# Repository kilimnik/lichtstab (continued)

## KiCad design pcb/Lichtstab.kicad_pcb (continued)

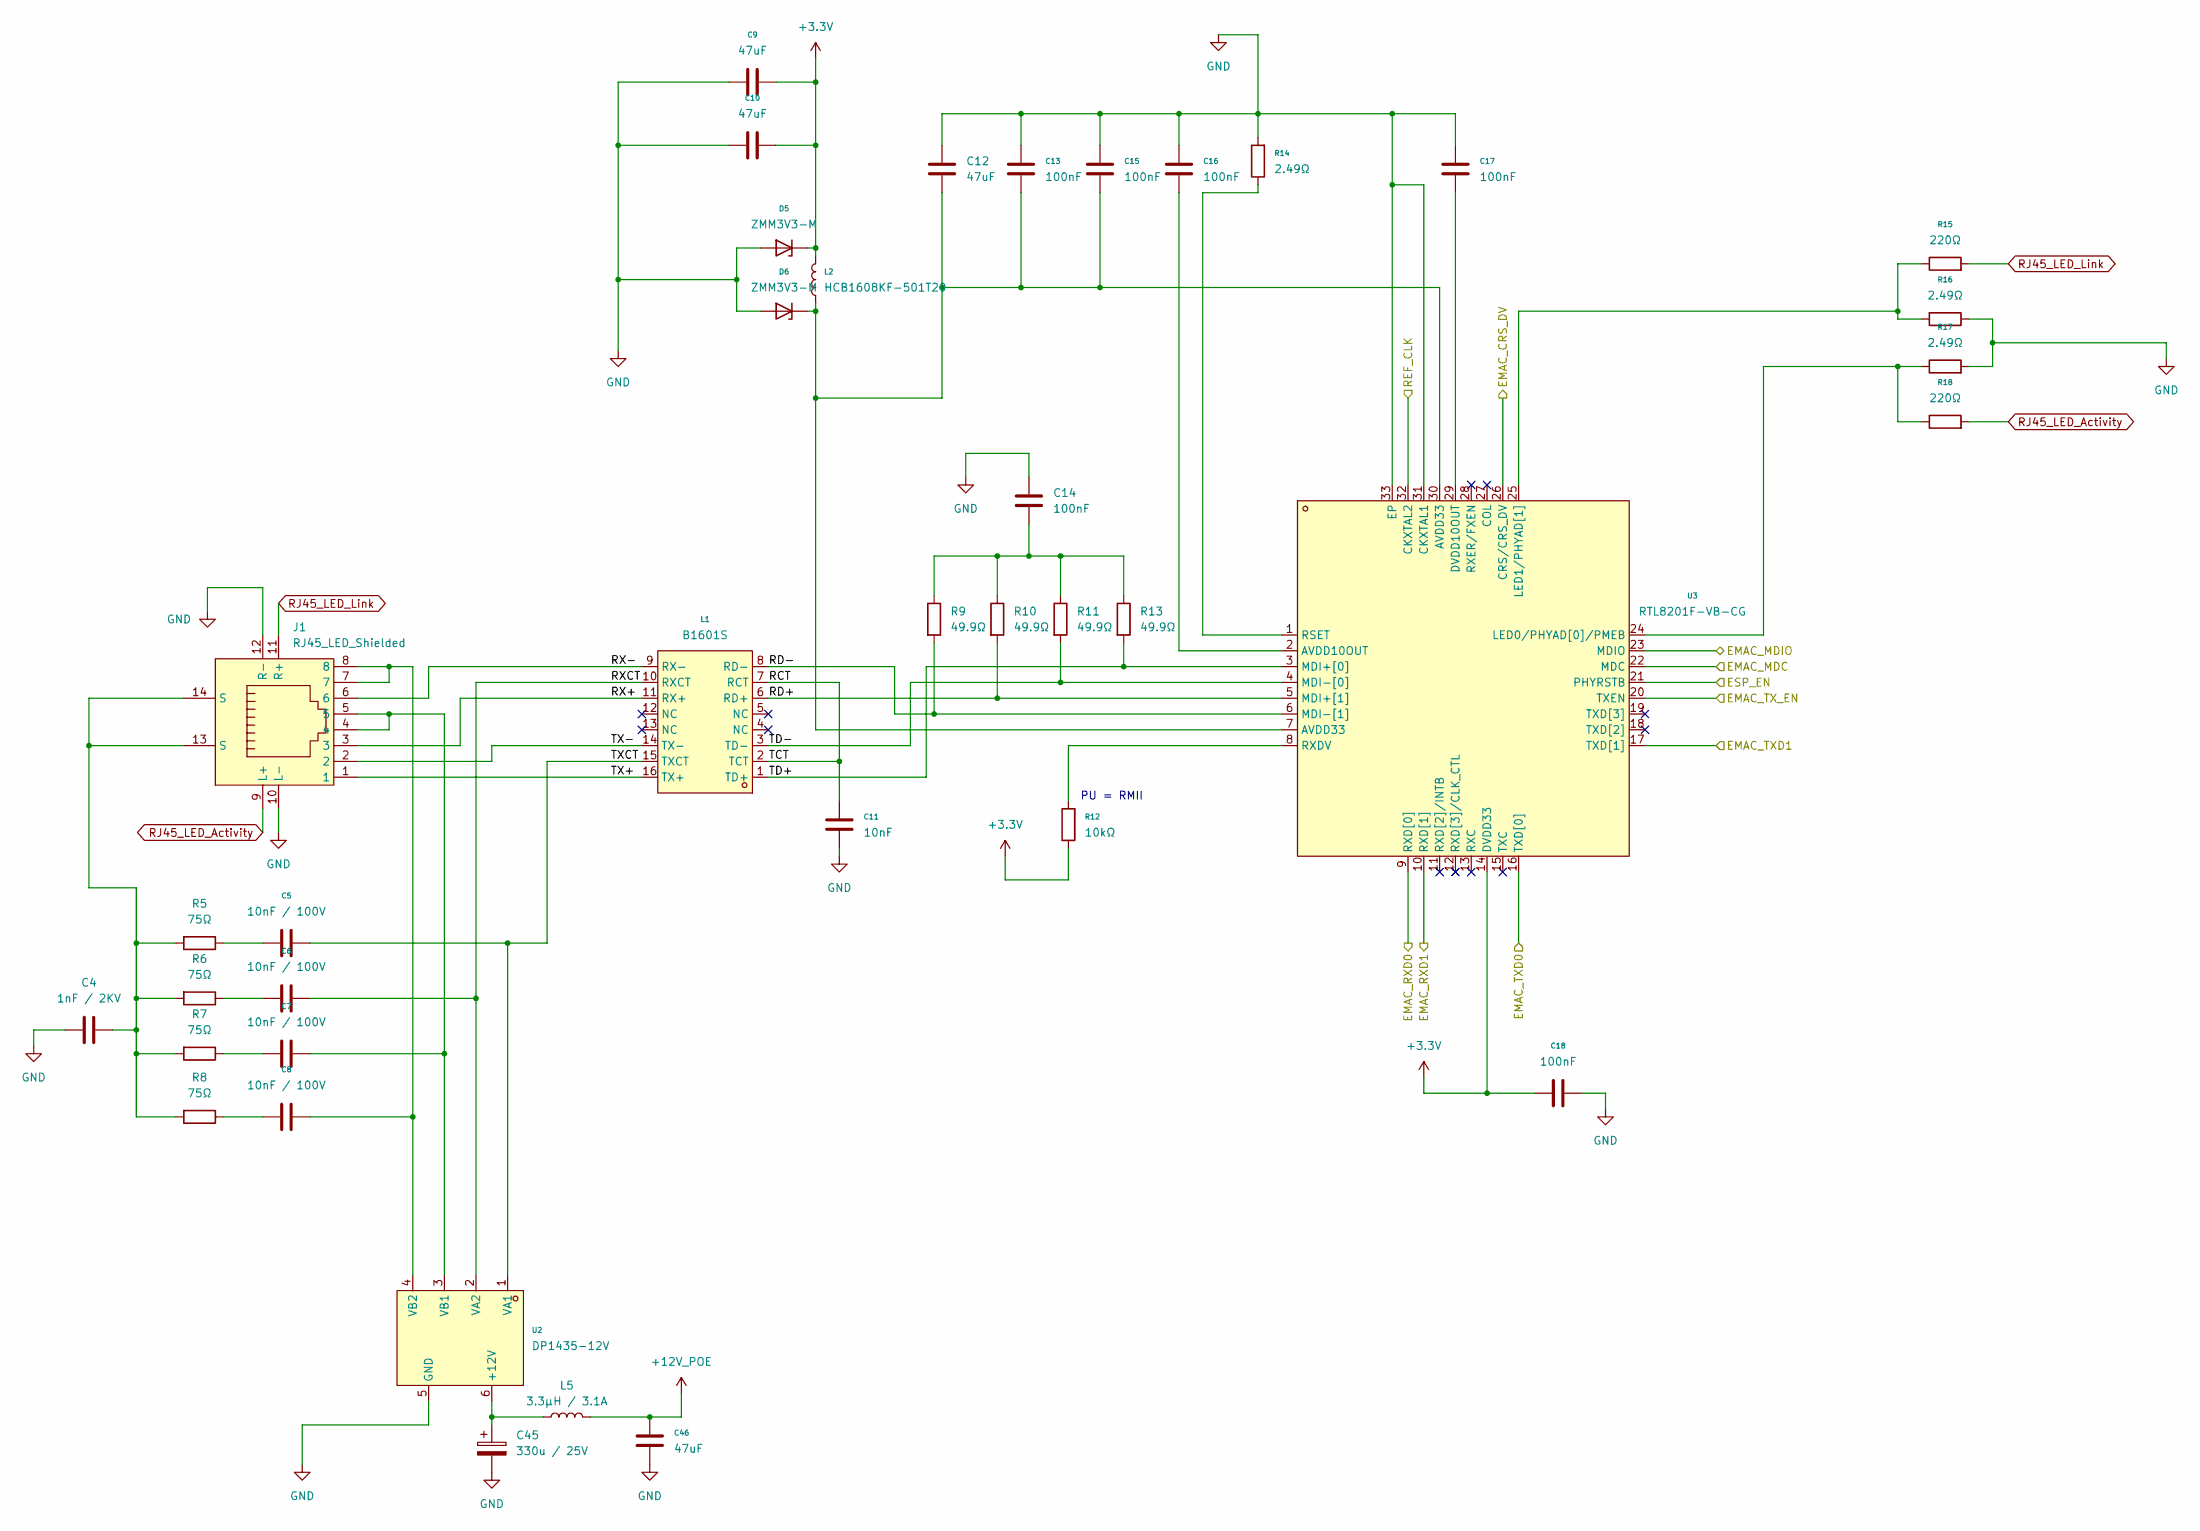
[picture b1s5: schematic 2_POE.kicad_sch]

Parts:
C4: 1nF / 2KV; C_1206_3216Metric
C5, C6, C7, C8: 10nF / 100V; C_0603_1608Metric; LCSC C43253
C9, C10, C12, C46: 47uF; C_1206_3216Metric; LCSC C22367835
C11: 10nF; C_0603_1608Metric; LCSC C43253
C13, C15, C16, C17, C18: 100nF; C_0603_1608Metric; LCSC C14663
C14: 100nF; C_0603_1608Metric
C45: 330u / 25V; CP_Elec_8x10.5; LCSC C335985
D5, D6: ZMM3V3-M; D_MiniMELF; LCSC C2891740
J1: RJ45_LED_Shielded; RJ45-TH_R-RJ45R08P-C000; LCSC Part C386757
L1: B1601S; SMD-16_L12.7-W7.0-P1.27-LS9.5-BL; LCSC C510548
L2: HCB1608KF-501T20; L_0603_1608Metric; LCSC C356977
L5: 3.3µH / 3.1A; L_Changjiang_FNR5030S; LCSC C2847470
R5, R6, R7, R8: 75Ω; R_0603_1608Metric; LCSC C4275
R9, R10, R11, R13: 49.9Ω; R_0402_1005Metric
R12: 10kΩ; R_0603_1608Metric; LCSC C25804
R14, R16, R17: 2.49Ω; R_0603_1608Metric; LCSC C22908
R15, R18: 220Ω; R_0603_1608Metric; LCSC C22962
U2: DP1435-12V; PWRM-TH_DP1435-XX; LCSC Part C5380098
U3: RTL8201F-VB-CG; TQFN-32-1EP_5x5mm_P0.5mm_EP3.4x3.4mm_ThermalVias; LCSC C45044

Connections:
+3.3V: C9.1, C10.1, C18.1, D5.1 (K), L2.2, R12.1, U3.14 (DVDD33); also elsewhere on the board
+12V_POE: C46.2, L5.2; also elsewhere on the board
/General/EMAC_CRS_DV: U3.26 (CRS/CRS_DV); also elsewhere on the board
/General/EMAC_MDC: U3.22 (MDC); also elsewhere on the board
/General/EMAC_MDIO: U3.23 (MDIO); also elsewhere on the board
/General/EMAC_RXD0: U3.9 (RXD[0]); also elsewhere on the board
/General/EMAC_RXD1: U3.10 (RXD[1]); also elsewhere on the board
/General/EMAC_TXD0: U3.16 (TXD[0]); also elsewhere on the board
/General/EMAC_TXD1: U3.17 (TXD[1]); also elsewhere on the board
/General/EMAC_TX_EN: U3.20 (TXEN); also elsewhere on the board
/General/ESP_EN: U3.21 (PHYRSTB); also elsewhere on the board
/General/REF_CLK: U3.32 (CKXTAL2); also elsewhere on the board
/POE/RCT: C11.2, L1.2 (TCT), L1.7 (RCT)
/POE/RD+: L1.6 (RD+), R10.2, U3.5 (MDI+[1])
/POE/RD-: L1.8 (RD-), R9.2, U3.6 (MDI-[1])
/POE/RX+: J1.3, L1.11 (RX+)
/POE/RX-: J1.6, L1.9 (RX-)
/POE/RXCT: C6.2, L1.10 (RXCT), U2.2 (VA2)
/POE/TD+: L1.1 (TD+), R13.2, U3.3 (MDI+[0])
/POE/TD-: L1.3 (TD-), R11.2, U3.4 (MDI-[0])
/POE/TX+: J1.1, L1.16 (TX+)
/POE/TX-: J1.2, L1.14 (TX-)
/POE/TXCT: C5.2, L1.15 (TXCT), U2.1 (VA1)
GND: C4.1, C9.2, C10.2, C11.1, C12.1, C13.1, C14.1, C15.1, C16.1, C17.1, C18.2, C45.2, C46.1, D5.2 (A), D6.2 (A), J1.10 (L-), J1.12 (R-), R14.2, R16.1, R17.2, U2.5 (GND), U3.31 (CKXTAL1), U3.33 (EP); also elsewhere on the board
unnamed: C4.2, J1.13 (S), J1.14 (S), R5.2, R6.2, R7.2, R8.2
unnamed: C5.1, R5.1
unnamed: C6.1, R6.1
unnamed: C7.1, R7.1
unnamed: C8.2, R8.1
unnamed: C14.2, R9.1, R10.1, R11.1, R13.1
unnamed: C12.2, C13.2, C15.2, D6.1 (K), L2.1, U3.7 (AVDD33), U3.30 (AVDD33)
unnamed: C45.1, L5.1, U2.6 (+12V)
unnamed: C7.2, J1.4, J1.5, U2.3 (VB1)
unnamed: C8.1, J1.7, J1.8, U2.4 (VB2)
unnamed: C16.2, U3.2 (AVDD10OUT)
unnamed: C17.2, U3.29 (DVDD10OUT)
unnamed: R17.1, R18.1, U3.24 (LED0/PHYAD[0]/PMEB)
unnamed: R15.1, R16.2, U3.25 (LED1/PHYAD[1])
unnamed: R14.1, U3.1 (RSET)
unnamed: R12.2, U3.8 (RXDV)
RJ45_LED_Activity: J1.9 (L+), R18.2
RJ45_LED_Link: J1.11 (R+), R15.2

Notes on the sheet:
PU = RMII

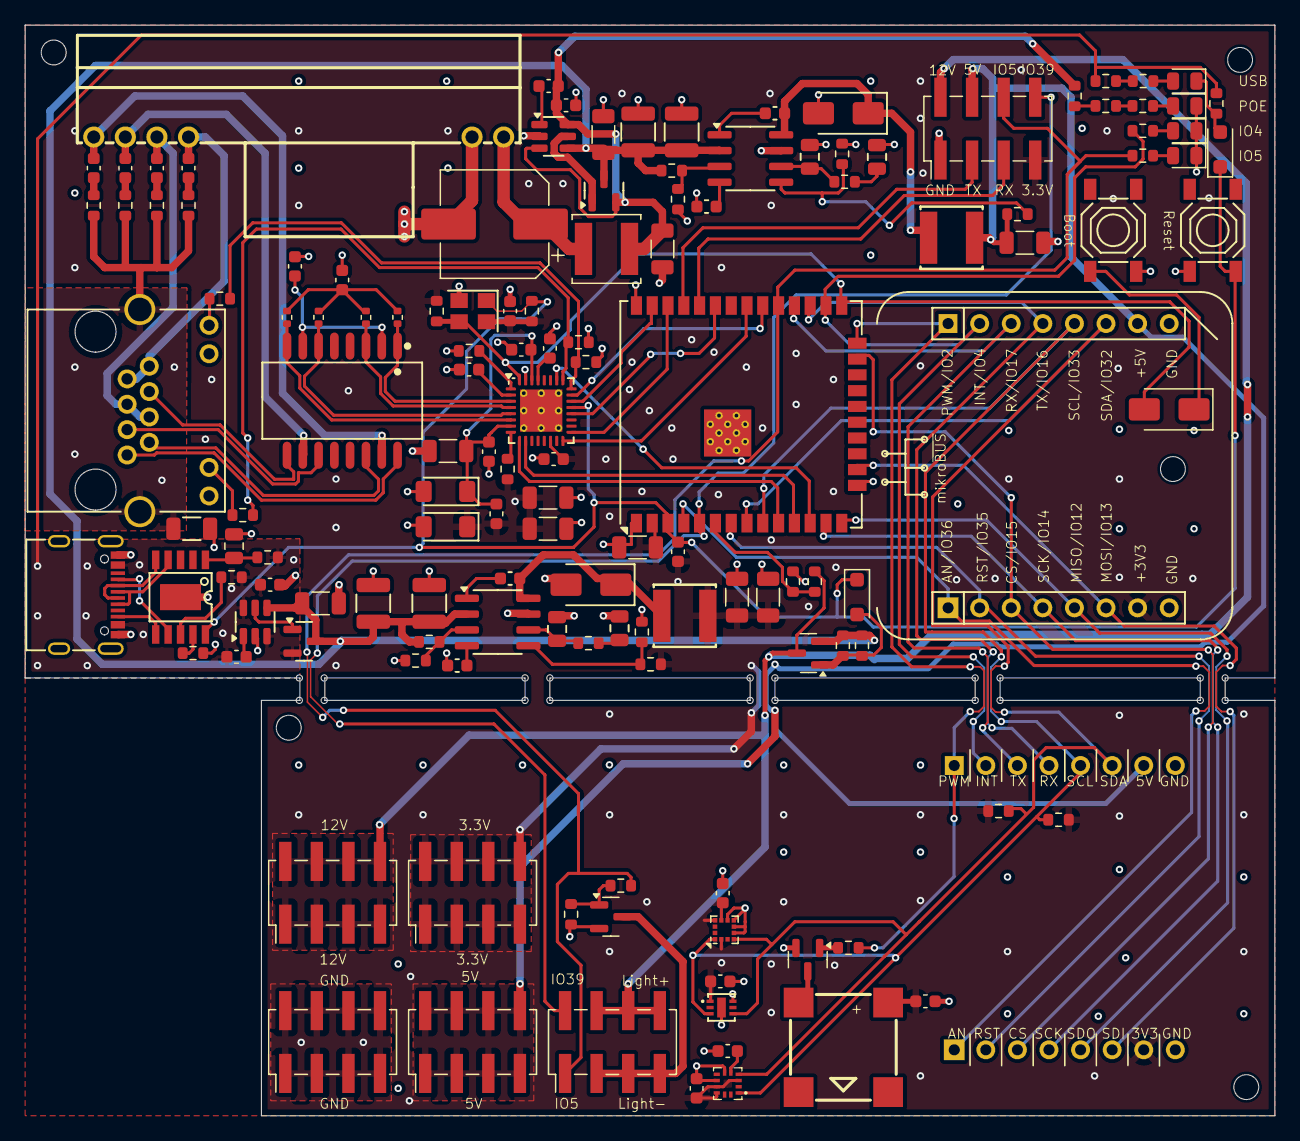
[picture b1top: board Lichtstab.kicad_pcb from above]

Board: 4 copper layers, 100.5 x 87.7 mm, 140 parts (1 on the bottom side), 103 nets.

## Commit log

2024-06-19 Initial
2024-06-23 4 layer pcb
2024-06-23 add mounting holes
2024-06-24 fix GXHTC3C pinout
2024-06-25 fix 3D Models
2024-06-25 fix holes
2024-06-25 review version
2024-06-26 remove third pcb and more flash
2024-06-27 add step file
